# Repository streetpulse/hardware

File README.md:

hardware
========

All hardware for streetpulse are presented in this folder: that's sensors, wireless communication and receiver.
all contents on this repository are under Creative commons (Attribution-NonCommercial-ShareAlike 3.0 Unported)

Sensors
========

The Sensors are composed of an electronic board, a battery, a solar cell and an enclosure.

You will find the PCB file (Eagle software) to make the electronic board for sensors from scratch, with the list of components used. Most manufacturers will take these files and can produce the sensor modules without additional work.

- garbageSensor.brd 
- garbageSensor.sch
- bom-street-pulse.xls
 
For the enclosure containing the modules, We used a **BUD CU-791-MB** but other boxes might do.

Regarding the solar cell, we imported a model from China, the **SZGD6060-4P**, but all models capable of 2Volts at 200mA max (max Power 0.4 Watt) would do.

Base
====
The "base" that receives data is a **Raspberry Pi** with an antenna and a wireless transceiver from [Sparkfun][https://www.sparkfun.com/products/705], see pictures in the base folder. Note that we first tried to use
an arduino wireless Shield for this (that's the picture) but  performance was too poor.

Aside from better performance, we also recommend the use of Raspberry Pi as it saves data locally before sending it to a server. 
This allowed us to cope with unreliable wifi connection and network loss of data. It also serves as additional backup.

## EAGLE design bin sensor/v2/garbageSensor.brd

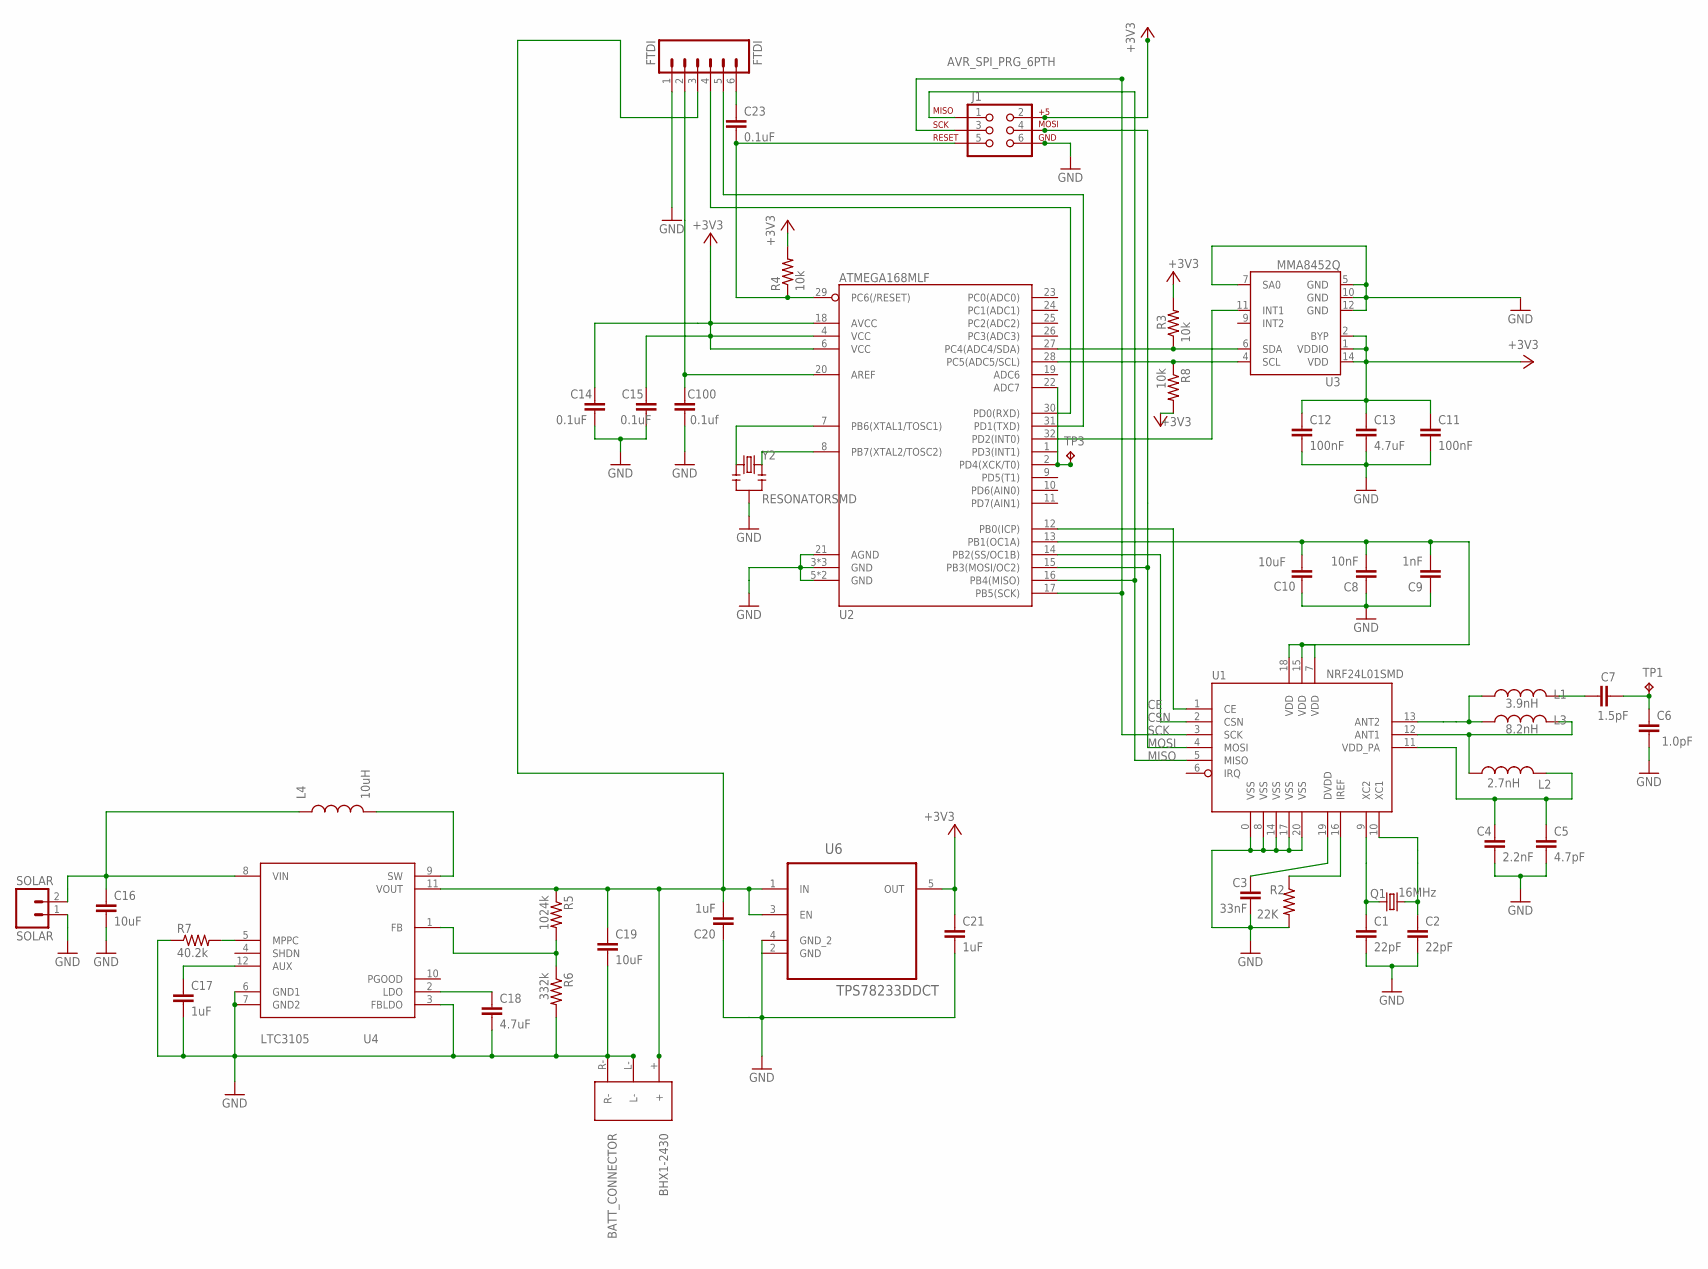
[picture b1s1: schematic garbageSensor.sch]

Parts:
B1: BATT_CONNECTOR; BHX1-2325
C1, C2: 22pF; 0603
C3: 33nF; 0603
C4: 2.2nF; C0402
C5: 4.7pF; C0402
C6: 1.0pF; C0402
C7: 1.5pF; C0402
C8: 10nF; 0603
C9: 1nF; 0603
C10, C16, C19: 10uF; C0603K
C11, C12: 100nF; C0603K
C13, C18: 4.7uF; C0603K
C14, C15: 0.1uF; C0603K
C17, C20, C21: 1uF; C0603K
C23: 0.1uF; 0603-CAP
C100: 0.1uf; 0603-CAP
FTDI: FTDI; 1X06
J1: AVR_SPI_PRG_6PTH; 2X3
L1: 3.9nH; C0402
L2: 2.7nH; C0402
L3: 8.2nH; C0402
L4: 10uH; 0806
Q1: 16MHz; CRYSTAL-SMD-5X3
R2: 22K; 0603
R3, R4, R8: 10k; R0603
R5: 1024k; R0603
R6: 332k; R0603
R7: 40.2k; R0603
SOLAR: SOLAR; 1X02_LOCK
TP1: TPB2,54; B2,54
TP3: TPTP06R; TP06R
U1: NRF24L01SMD; QFN20
U2: ATMEGA168MLF; MLF32
U3: MMA8452Q; QFN-16_0.5MM
U4: CHARGER; MSOP-12
U6: TPS78233DDCT; SOT95P280X110-5N
Y2: RESONATORSMD; RESONATOR-SMD

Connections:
+3V3: C11.1, C12.1, C13.1, C14.2, C15.2, C21.1, J1.2, R3.2, R4.2, R8.2, U2.4 (VCC), U2.6 (VCC), U2.18 (AVCC), U3.1 (VDDIO), U3.2 (BYP), U3.14 (VDD), U6.5 (OUT)
ACCELERO_INTERRUPT: U2.32 (PD2(INT0)), U3.11 (INT1)
ANT: C6.2, C7.2, TP1.TP
ANTENNA1: L1.1, L3.1, U1.13 (ANT2)
ANTENNA2: L2.1, L3.2, U1.12 (ANT1)
ANTENNA3: C4.1, C5.1, L2.2, U1.11 (VDD_PA)
AREF: C100.1, FTDI.2, U2.20 (AREF)
AUX: C17.1, U4.12 (AUX)
CE: U1.1 (CE), U2.12 (PB0(ICP))
CSN: U1.2 (CSN), U2.14 (PB2(SS/OC1B))
FB: R5.2, R6.1, U4.1 (FB)
GND: B1.L-, B1.R-, C1.2, C2.2, C3.2, C4.2, C5.2, C6.1, C8.1, C9.1, C10.2, C11.2, C12.2, C13.2, C14.1, C15.1, C16.2, C17.2, C18.2, C19.2, C20.1, C21.2, C100.2, FTDI.1, J1.6, R2.2, R6.2, R7.1, SOLAR.1, U1.0 (VSS), U1.8 (VSS), U1.14 (VSS), U1.17 (VSS), U1.20 (VSS), U2.3 (GND), U2.5 (GND), U2.21 (AGND), U2.GND1 (GND), U2.GND2 (GND), U2.GND3 (GND), U3.5 (GND), U3.7 (SA0), U3.10 (GND), U3.12 (GND), U4.3 (FBLDO), U4.6 (GND1), U4.7 (GND2), U6.2 (GND), U6.4 (GND_2), Y2.2
LDO: C18.1, U4.2 (LDO)
MISO: J1.1, U1.5 (MISO), U2.16 (PB4(MISO))
MOSI: J1.4, U1.4 (MOSI), U2.15 (PB3(MOSI/OC2))
MPPC: R7.2, U4.5 (MPPC)
unnamed: C1.1, Q1.1, U1.9 (XC2)
unnamed: C2.1, Q1.3 (2), U1.10 (XC1)
unnamed: R2.1, U1.16 (IREF)
unnamed: C3.1, U1.19 (DVDD)
unnamed: TP3.TP, U2.2 (PD4(XCK/T0))
unnamed: C7.1, L1.2
unnamed: L4.P$2 (2), U4.9 (SW)
unnamed: C23.1, FTDI.6
RESET: C23.2, J1.5, R4.1, U2.29 (PC6(/RESET))
RX: FTDI.4, U2.30 (PD0(RXD))
SCK: J1.3, U1.3 (SCK), U2.17 (PB5(SCK))
SCL: R8.1, U2.28 (PC5(ADC5/SCL)), U3.4 (SCL)
SDA: R3.1, U2.27 (PC4(ADC4/SDA)), U3.6 (SDA)
SOLAR: C16.1, L4.P$1 (1), SOLAR.2, U4.8 (VIN)
TX: FTDI.5, U2.31 (PD1(TXD))
VBATT: B1.+, C19.1, C20.2, FTDI.3, R5.1, U4.11 (VOUT), U6.1 (IN), U6.3 (EN)
WIRELESS_POWER_LINE: C8.2, C9.2, C10.1, U1.7 (VDD), U1.15 (VDD), U1.18 (VDD), U2.13 (PB1(OC1A))
XTAL1: U2.7 (PB6(XTAL1/TOSC1)), Y2.1
XTAL2: U2.8 (PB7(XTAL2/TOSC2)), Y2.3

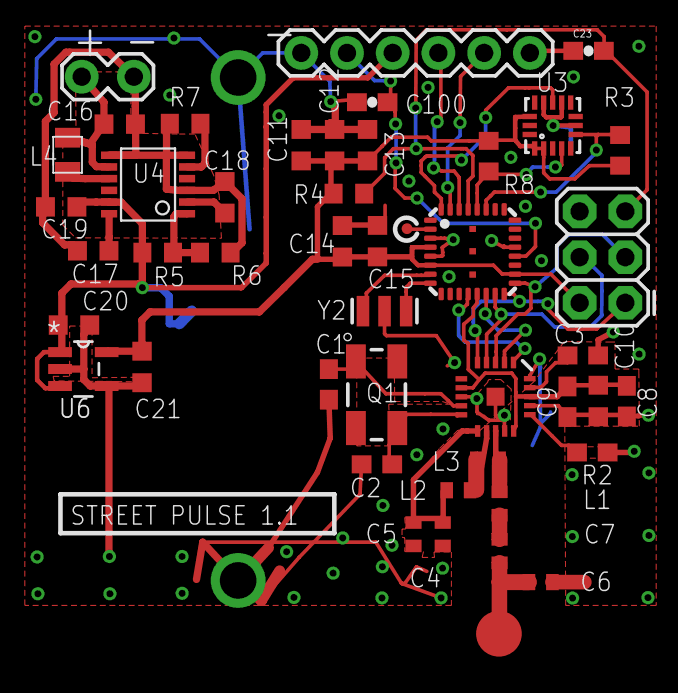
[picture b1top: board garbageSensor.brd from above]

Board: 2 copper layers, 47 parts (1 on the bottom side), 35 nets.

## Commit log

2013-06-07 board layout
2013-06-07 added base info + images
2013-08-27 updated newest hardware design
    - re-made repository structure for versions
    - added new image from latest hardware
    - added newest design files for hardware design
2013-09-11 added markdown elements
2013-09-11 corrected markdown
2013-09-11 updated markdown
2013-09-11 added CC licence
2014-02-06 prettified the read me

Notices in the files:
README.md:
CC BY-NC-SA 3.0
parts and their libraries:
SparkFun-DigitalIC: Licensing: CC v3.0 Share-Alike You are welcome to use this library for commercial purposes.
